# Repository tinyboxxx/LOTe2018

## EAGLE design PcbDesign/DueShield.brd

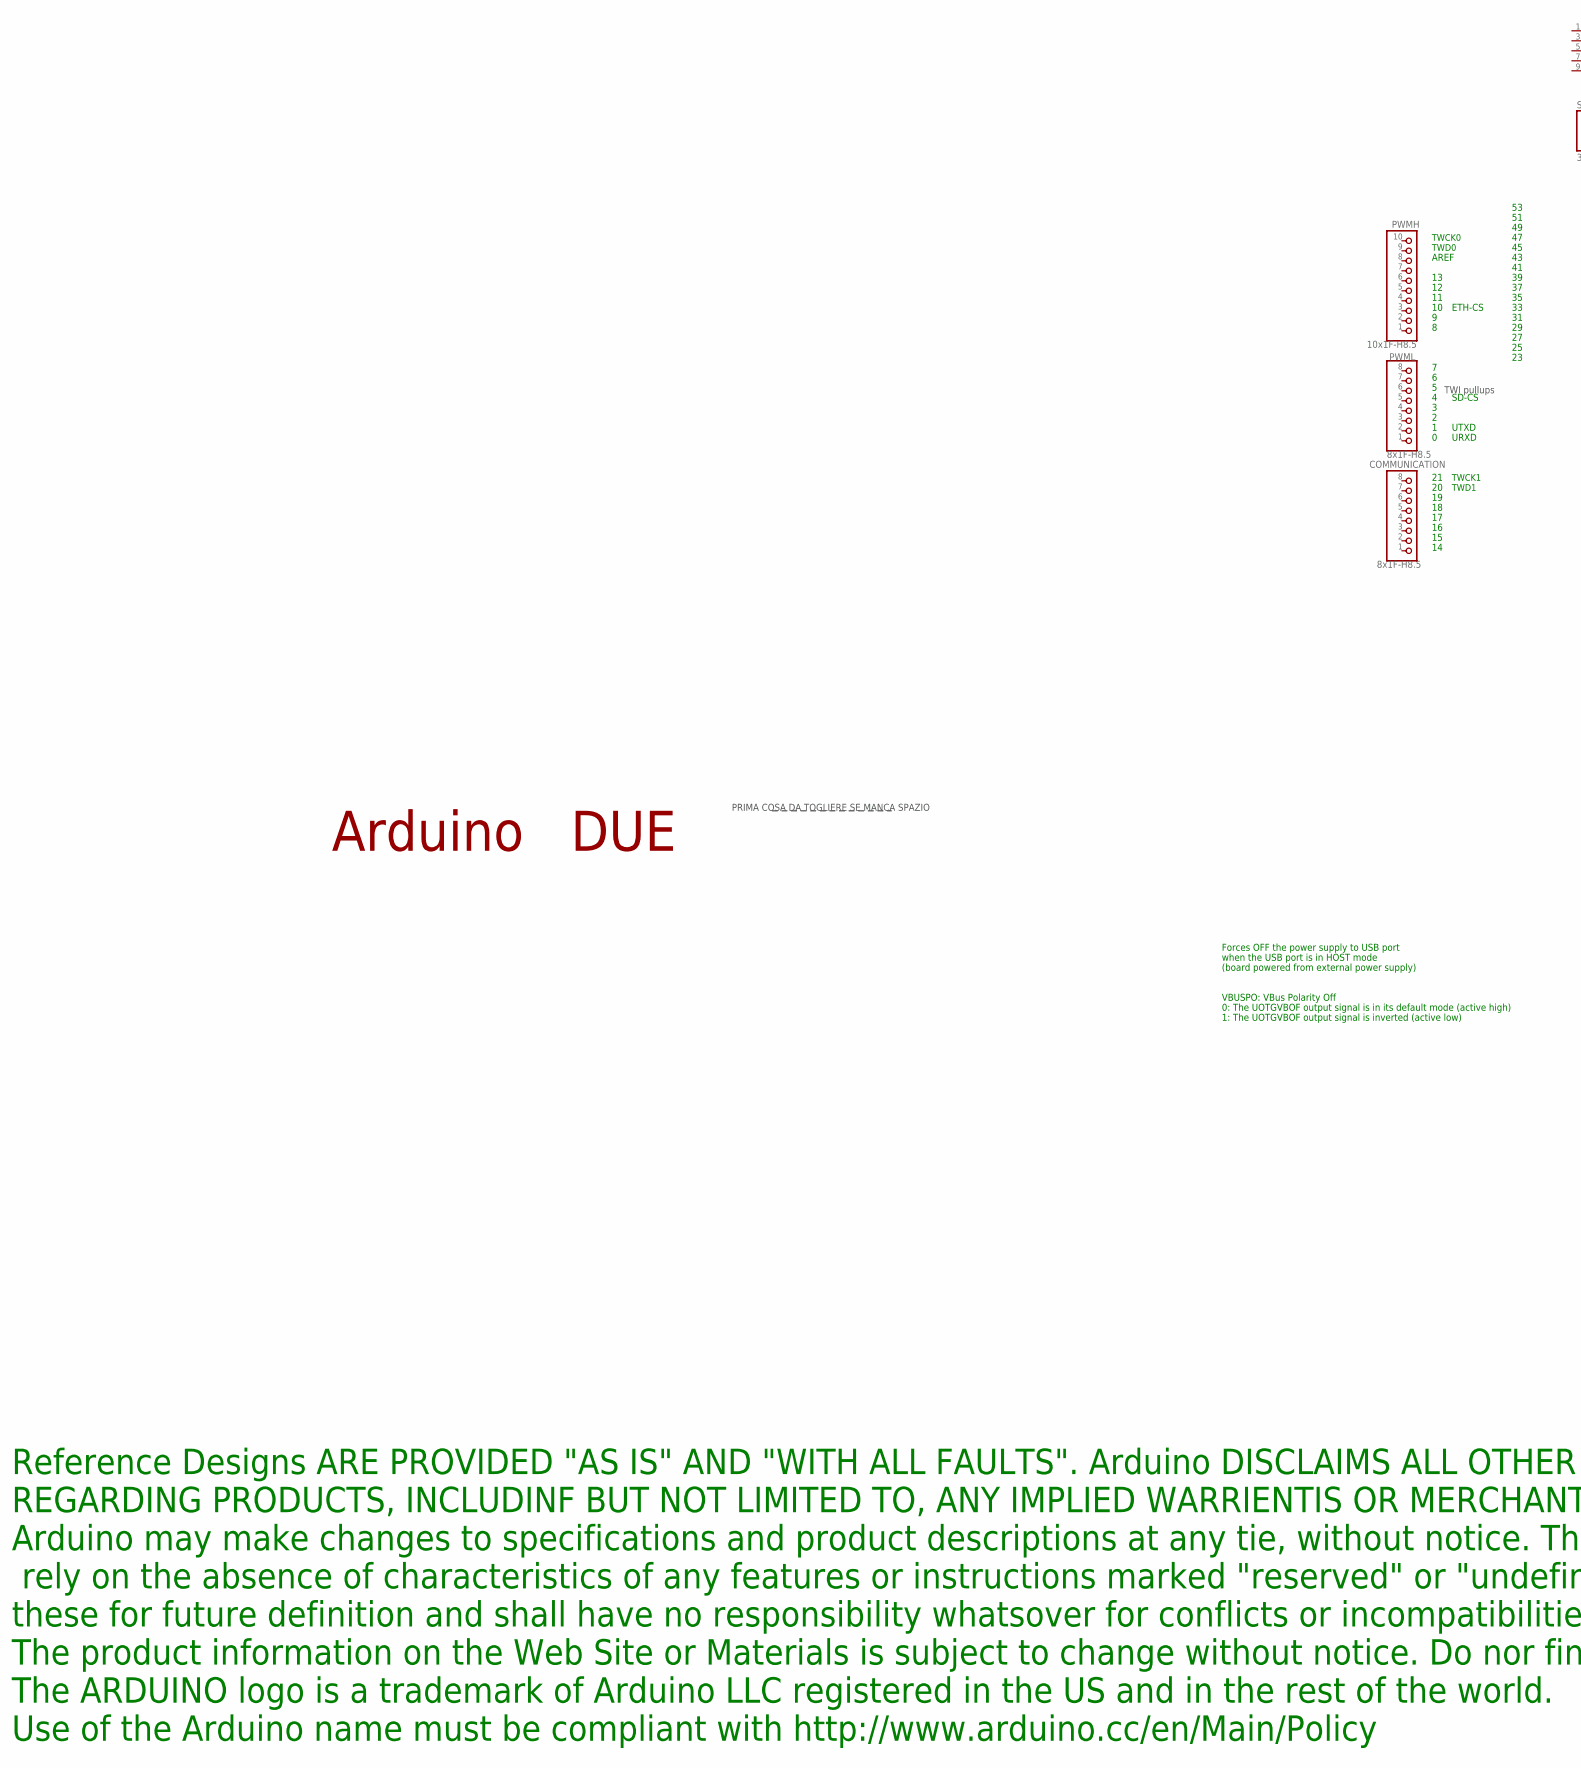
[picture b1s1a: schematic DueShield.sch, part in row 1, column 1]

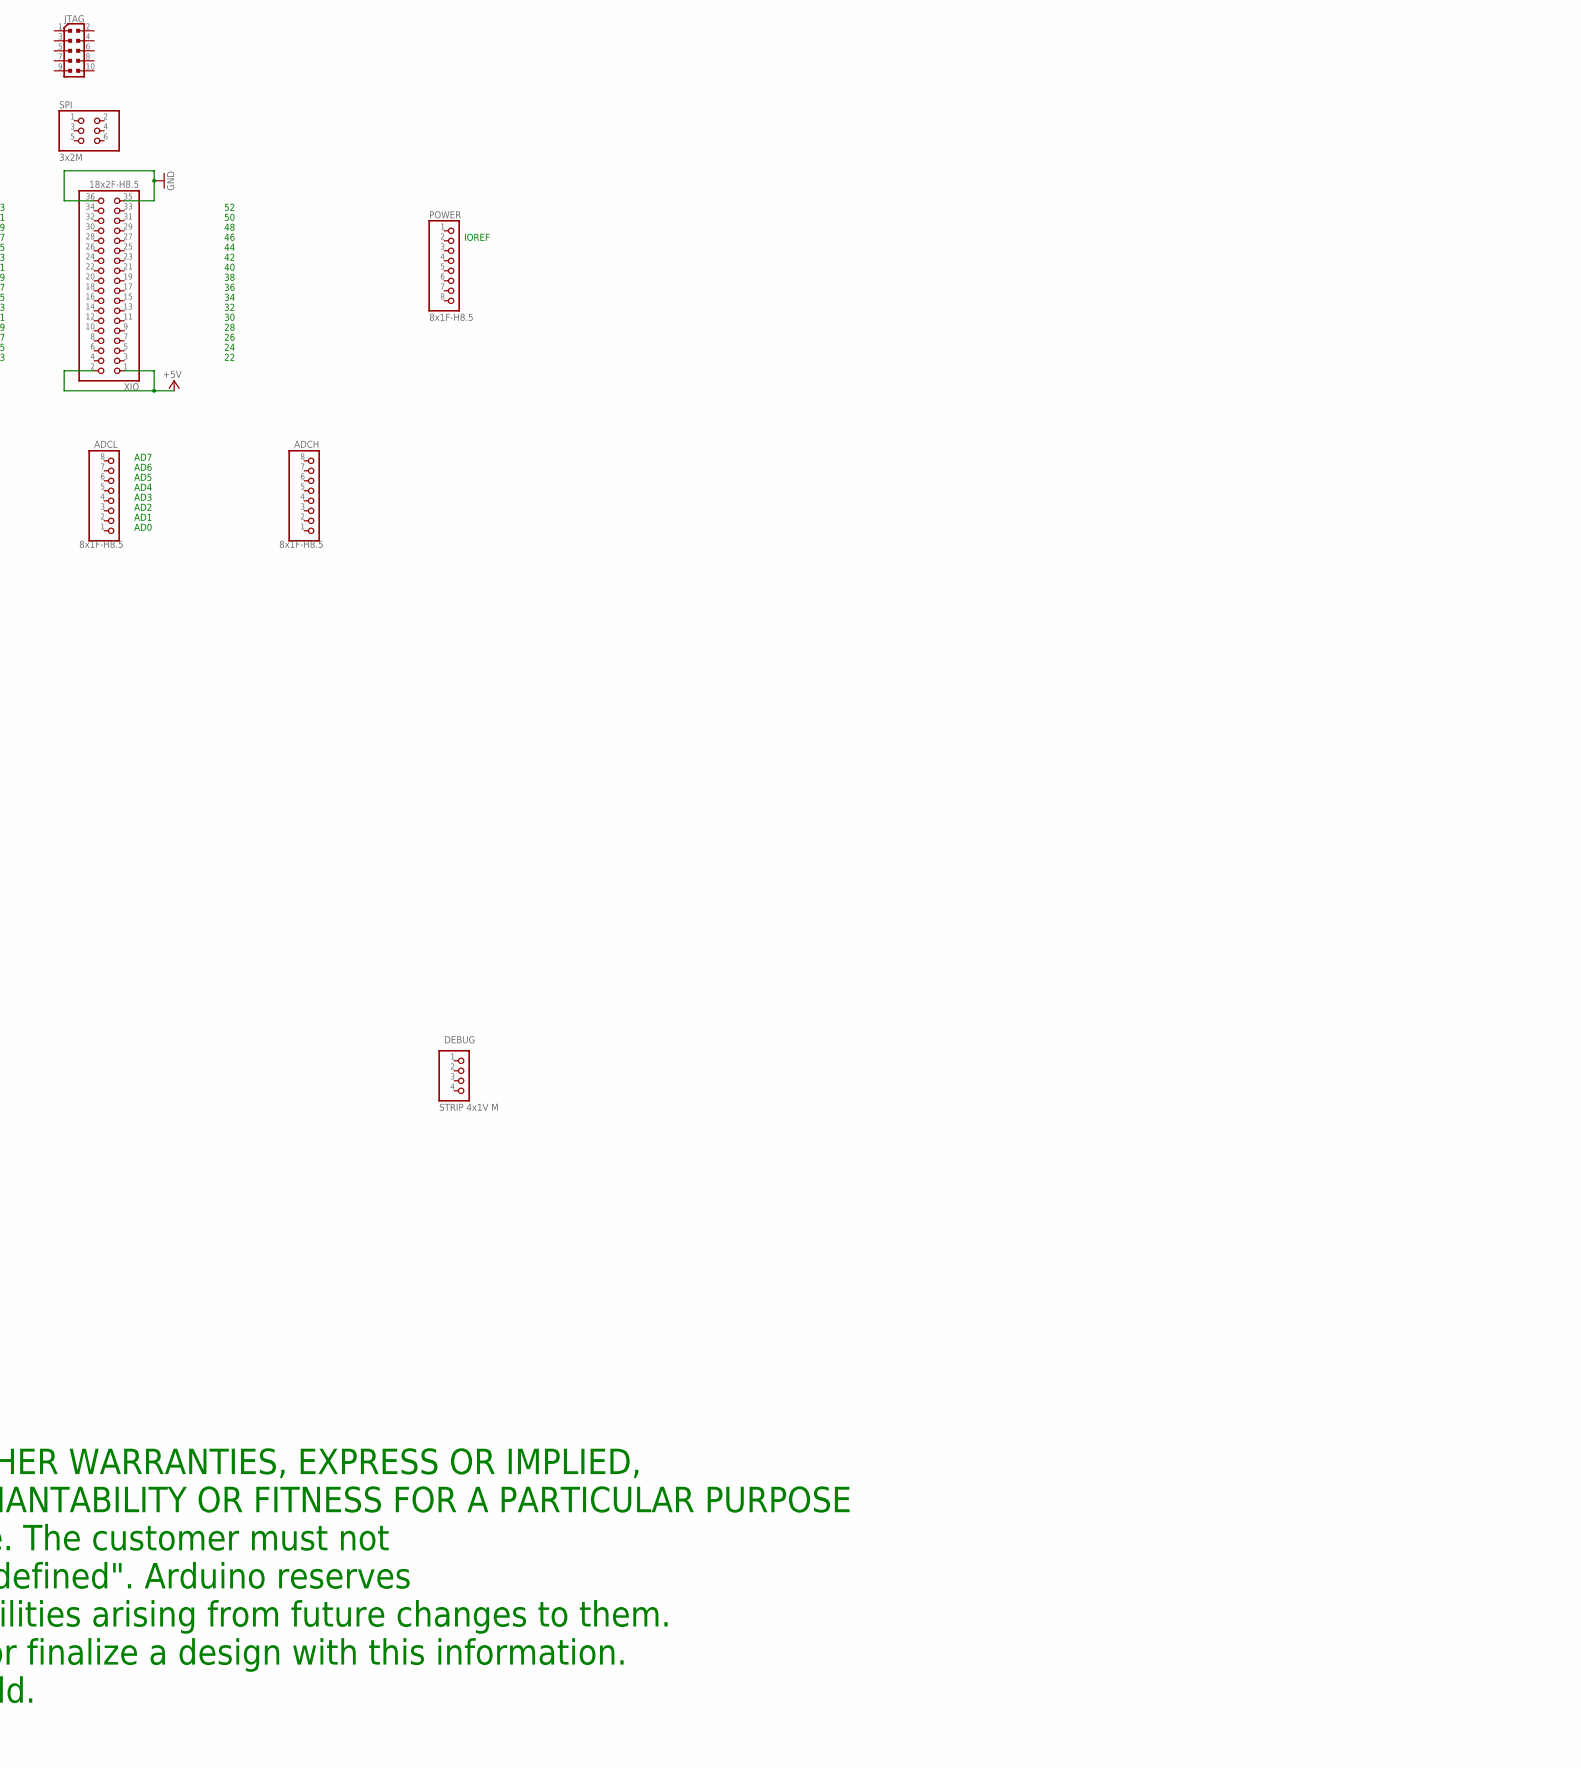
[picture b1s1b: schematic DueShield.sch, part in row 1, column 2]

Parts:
ADCH: 8x1F-H8.5; 1X08
ADCL: 8x1F-H8.5; 1X08
COMMUNICATION: 8x1F-H8.5; 1X08
DEBUG: STRIP 4x1V M; 1X04
JTAG: PINHEAD_PINHD-2X5PASSO127; PINHEAD_2X05_127
POWER: 8x1F-H8.5; 1X08
PWMH: 10x1F-H8.5; 1X10
PWML: 8x1F-H8.5; 1X08
SPI: 3x2M; 2X03
XIO: 18x2F-H8.5; 2X18

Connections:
+5V: XIO.1, XIO.2
GND: XIO.35, XIO.36

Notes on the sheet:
TWI pullups
TWCK1
TWD1
IOREF
TWCK0
TWD0
AD1
AD2
AD3
AD4
AD5
AD6
AD0
AREF
AD7
SD-CS
Forces OFF the power supply to USB port
when the USB port is in HOST mode
(board powered from external power supply)
VBUSPO: VBus Polarity Off
0: The UOTGVBOF output signal is in its default mode (active high)
1: The UOTGVBOF output signal is inverted (active low)
UTXD
URXD
ETH-CS
PRIMA COSA DA TOGLIERE SE MANCA SPAZIO
Arduino DUE
Reference Designs ARE PROVIDED "AS IS" AND "WITH ALL FAULTS". Arduino DISCLAIMS ALL OTHER WARRANTIES, EXPRESS OR IMPLIED, REGARDING PRODUCTS, INCLUDINF BUT NOT LIMITED TO, ANY IMPLIED WARRIENTIS OR MERCHANTABILITY OR FITNESS FOR A PARTICULAR PURPOSE Arduino may make changes to specifications and pr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

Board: 2 copper layers, 10 parts (0 on the bottom side), 2 nets, no tracks yet.

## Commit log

2018-03-12 add led test to check
2018-03-12 add graphicstest
    only soft spi usable
2018-03-12 migrate old doce
2018-03-12 change origin code
2018-03-12 minor fix
2018-03-13 delay fix
2018-03-13 rebuild to full buffer
2018-03-14 not sure if bootbmp works
2018-03-14 add data process
2018-03-14 add timer
2018-03-14 testing
2018-03-14 enable 16bit
2018-03-14 change to print
2018-03-14 bugfix!works!
2018-03-16 add gpscalculate
2018-03-17 serial send test
2018-03-17 add rpm gps support
2018-03-17 GPSfix
2018-04-10 serial update
2018-04-13 fromRPM update
2018-04-14 no change
2018-04-14 add time
2018-04-14 gpsupdate
2018-04-14 format update
2018-04-14 u8g2library update
2018-04-14 u8g2 16bit update
2018-04-14 temperature update
2018-04-14 change scan
2018-04-24 use no gps date
2018-04-27 bmx055 added
2018-04-30 try-with-no-library
2018-05-03 add eagle file
2018-05-07 try to get acc work
2018-05-07 add new acc sensor
2018-06-15 speed calculation
2018-06-19 volt and wireless improvement
2018-06-19 merge
2018-07-11 parseInt
2018-07-30 7.30 nano fixed, oled rebuilded not sure
2019-10-17 misc update
2019-10-17 2020 Project Start
    will based on Teensy4.0 and more advanced sensors and communication structures.
2019-10-17 Library and Reference Added
2019-10-17 REF update
2019-10-18 更新至最新的版本 Updated to latest version
    这应该是目前能找到当时搭载在车上最新的版本了。
    This should be the latest version that can be found.
2019-10-18 Delete OledDueRebuild.ino
    revert unwanted change
2019-10-18 Create e2020Docs
2019-10-18 Rename e2020Docs/FRAME.md to e2020Doc/FRAME.md
2020-01-20 regular update
2020-01-21 gps and oled works
2020-01-21 SDTestWorks
